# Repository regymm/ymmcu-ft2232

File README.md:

## YMMCU-FT2232HL

#### Function

Can be used as Xilinx JTAG downloader & USB-to-UART bridge simultaneously following [this](https://gist.github.com/rikka0w0/24b58b54473227502fa0334bbe75c3c1). 

Partly pin-to-pin compatible with the CJMCU FT232HL(the purple PCB one) and has a standard 2x7 JTAG connector. 

Main chips: FT2232HL(QFP64), ASM1117(3.3V, SOT89), 93LC56(SOP8). 

Micro-USB + Type-C(tested later so not shown on pic) connection. 

Made with Kicad. 

#### Gallery

#### License

GPL-v3

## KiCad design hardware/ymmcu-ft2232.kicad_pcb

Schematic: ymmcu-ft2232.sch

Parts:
C1: 0805_1nF__102_10%_50V; C_0603_1608Metric
C2, C3: 0805_27pF__270_5%_50V; C_0603_1608Metric
C4, C5, C6, C7, C8, C10, C11, C12, C13, C14, C15, C16, C17, C18, C19, C20, C21: 1206_100nF__104_10%_50V; C_0603_1608Metric
C9: 0805_3.3nF__332_10%_50V; C_0603_1608Metric
D1: TXLED; LED_0603_1608Metric
D2: RXLED; LED_0603_1608Metric
D3: PWRLED; LED_0603_1608Metric
FB1, FB2, FB3: FBEAD_SMD_BLM21PG221SN1D; L_0603_1608Metric
J1: 2x7 JTAG; PinHeader_2x07_P2.54mm_Vertical
J2: UART; PinHeader_1x10_P2.54mm_Vertical
J3: JTAG; PinHeader_1x10_P2.54mm_Vertical
J4: PWR; PinHeader_1x04_P2.54mm_Vertical
J5: USB_B_Micro; USB_Micro-B_Amphenol_10118194_Horizontal
J6: USB_C_Receptacle_USB2.0; USB_C_Receptacle_GCT_USB4085
R1: 0805_1MΩ__1004_1%; R_0603_1608Metric
R2, R3, R5: 1206_10KΩ__1002_1%; R_0603_1608Metric
R4: 1206_2KΩ__2001_1%; R_0603_1608Metric
R6, R7, R12: 0805_330Ω__3300_1%; R_0603_1608Metric
R8: 0805_12KΩ__1202_1%; R_0603_1608Metric
R9: 1206_1KΩ__1001_1%; R_0603_1608Metric
R10, R11: 0805_5.1KΩ__5101_1%; R_0603_1608Metric
TP_NSUSP1: TESTPOINT_SMD_C1; TestPoint_Pad_D1.0mm
TP_NWREN1: TESTPOINT_SMD_C1; TestPoint_Pad_D1.0mm
U1: FT2232HL; LQFP-64_10x10mm_P0.5mm
U2: 93LC56BISN; SOP-8_3.9x4.9mm_P1.27mm
VR1: SOT-223_AMS1117-3.3; SOT-223
X1: XTL_4_12MHz_3225; Crystal_SMD_3225-4Pin_3.2x2.5mm

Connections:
/1V8: C9.2, C17.2, C18.2, C19.2, J4.3, U1.12, U1.37, U1.49, U1.64
/3V3: C4.1, C5.1, C7.1, C10.2, C12.2, C13.2, C14.2, C15.2, C16.2, FB1.1, FB2.1, J1.2, J4.2, R2.1, R3.1, R5.1, R6.2, R7.2, R9.2, R12.2, U1.20, U1.31, U1.42, U1.50, U1.56, U2.8, VR1.2
/5V0: C21.1, FB3.2, J3.2, J4.1
/AD0_TCK: J1.6, J3.10, U1.16
/AD1_TDI: J1.10, J3.9, U1.17
/AD2_TDO: J1.8, J3.8, U1.18
/AD3_TMS: J1.4, J3.7, U1.19
/AD4: J3.6, U1.21
/AD5: J3.5, U1.22
/AD6: J3.4, U1.23
/AD7: J3.3, U1.24
/BC3_RXLED: D2.1, U1.54
/BC4_TXLED: D1.1, U1.55
/BD0_TX: J2.10, U1.38
/BD1_RX: J2.9, U1.39
/BD2: J2.8, U1.40
/BD3: J2.7, U1.41
/BD4: J2.6, U1.43
/BD5: J2.5, U1.44
/BD6: J2.4, U1.45
/BD7: J2.3, U1.46
/CC1: J6.A5, R10.1
/CC2: J6.B5, R11.1
/EECLK: R3.2, U1.62, U2.2
/EECS: R2.2, U1.63, U2.1
/EEDATA: R4.2, R5.2, U1.61, U2.3
/GND: C1.2, C2.2, C3.2, C4.2, C5.2, C6.2, C7.2, C8.2, C9.1, C10.1, C11.1, C12.1, C13.1, C14.1, C15.1, C16.1, C17.1, C18.1, C19.1, C20.2, C21.2, D3.1, J1.1, J1.3, J1.5, J1.7, J1.9, J1.11, J1.13, J3.1, J4.4, J5.5, J6.A1, J6.A12, J6.B1, J6.B12, R1.1, R8.1, R10.2, R11.2, U1.1, U1.5, U1.10, U1.11, U1.13, U1.15, U1.25, U1.35, U1.47, U1.51, U2.5, VR1.1, X1.2, X1.4
/USB5V: C11.2, C20.1, FB3.1, J5.1, J6.A4, J6.A9, J6.B4, J6.B9, VR1.3
/USBDN: J5.2, J6.A7, J6.B7, U1.7
/USBDP: J5.3, J6.A6, J6.B6, U1.8
/USBSH: C1.1, J5.6, J6.S1, R1.2
/VPHY: C8.1, FB2.2, U1.4
/VPLL: C6.1, FB1.2, U1.9
/XTAL_N: C2.1, U1.2, X1.1
/XTAL_P: C3.1, U1.3, X1.3
/nPWREN: TP_NWREN1.1, U1.60
/nSUSP: TP_NSUSP1.1, U1.36
unnamed: D1.2, R6.1
unnamed: D2.2, R7.1
unnamed: D3.2, R12.1
unnamed: R4.1, U2.4
unnamed: R8.2, U1.6
unnamed: R9.1, U1.14

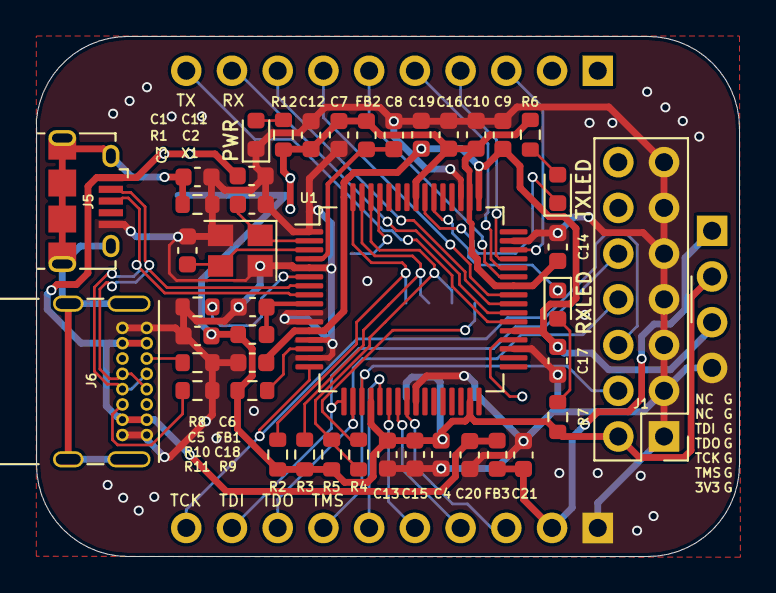
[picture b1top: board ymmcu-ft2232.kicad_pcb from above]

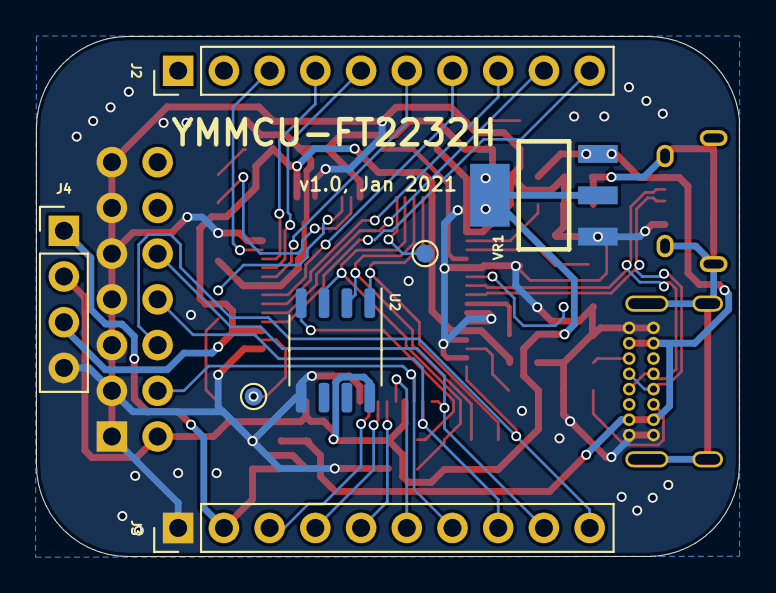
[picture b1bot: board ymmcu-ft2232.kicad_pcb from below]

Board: 2 copper layers, 39.1 x 28.9 mm, 51 parts (7 on the bottom side), 43 nets.

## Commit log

2021-01-24 Continue working
2021-03-21 Ready.
2021-06-22 Create LICENSE
2021-07-18 README modified
